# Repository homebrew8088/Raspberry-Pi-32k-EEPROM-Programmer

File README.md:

# Raspberry-Pi-32k-EEPROM-Programmer

\
\
This is a repository for my Rapberry Pi 32k EEPROM Programmer.

The [code](https://github.com/homebrew8088/Raspberry-Pi-32k-EEPROM-Programmer/tree/main/py) is written in python. To run it from the command line type "python3 32k.py"

I have included my [Kicad Files](https://github.com/homebrew8088/Raspberry-Pi-32k-EEPROM-Programmer/tree/main/Kicad) where you can find the schematics and PCB layout.

https://www.homebrew8088.com/home/28c256-eeprom-writer

This was developed to be a cheap alternative for writing 32k EEPROMs for my 8088 projects. You can compile and upload code in the application or just upload a precompiled file.  When using the application to compile the JMP code for an 8088 is automatically inserted at address 0x7FF0.  

The project uses\
1 - Raspberry PI\
2 - MCP23S17 SPI I/O’s\
1 - 28 pin ZIF\
1 - PCB\
3 - 10k resistors 

Trouble shoot \
-make sure SPI is enabled on the raspberry pi \
-install nasm on the raspberry pi

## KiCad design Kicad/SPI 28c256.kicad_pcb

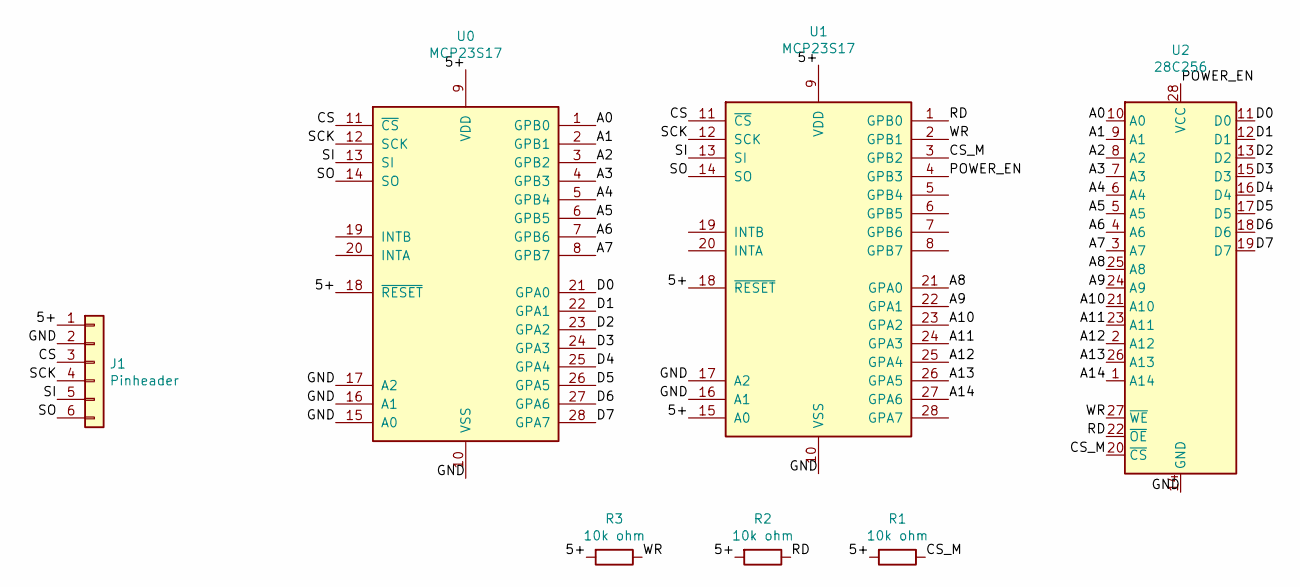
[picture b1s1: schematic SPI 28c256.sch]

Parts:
J1: Pinheader; PinHeader_1x06_P2.54mm_Vertical
R1, R2, R3: 10k ohm; R_Axial_DIN0207_L6.3mm_D2.5mm_P10.16mm_Horizontal
U0, U1: MCP23S17; DIP-28_W7.62mm
U2: 28C256; DIP_Socket-28_W11.9_W12.7_W15.24_W17.78_W18.5_3M_228-1277-0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

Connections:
/5+: J1.1, R1.2, R2.2, R3.2, U0.9 (VDD), U0.18 (~RESET~), U1.9 (VDD), U1.15 (A0), U1.18 (~RESET~)
/A0: U0.1 (GPB0), U2.10 (A0)
/A1: U0.2 (GPB1), U2.9 (A1)
/A2: U0.3 (GPB2), U2.8 (A2)
/A3: U0.4 (GPB3), U2.7 (A3)
/A4: U0.5 (GPB4), U2.6 (A4)
/A5: U0.6 (GPB5), U2.5 (A5)
/A6: U0.7 (GPB6), U2.4 (A6)
/A7: U0.8 (GPB7), U2.3 (A7)
/A8: U1.21 (GPA0), U2.25 (A8)
/A9: U1.22 (GPA1), U2.24 (A9)
/A10: U1.23 (GPA2), U2.21 (A10)
/A11: U1.24 (GPA3), U2.23 (A11)
/A12: U1.25 (GPA4), U2.2 (A12)
/A13: U1.26 (GPA5), U2.26 (A13)
/A14: U1.27 (GPA6), U2.1 (A14)
/CS: J1.3, U0.11 (~CS~), U1.11 (~CS~)
/CS_M: R1.1, U1.3 (GPB2), U2.20 (~CS)
/D0: U0.21 (GPA0), U2.11 (D0)
/D1: U0.22 (GPA1), U2.12 (D1)
/D2: U0.23 (GPA2), U2.13 (D2)
/D3: U0.24 (GPA3), U2.15 (D3)
/D4: U0.25 (GPA4), U2.16 (D4)
/D5: U0.26 (GPA5), U2.17 (D5)
/D6: U0.27 (GPA6), U2.18 (D6)
/D7: U0.28 (GPA7), U2.19 (D7)
/GND: J1.2, U0.10 (VSS), U0.15 (A0), U0.16 (A1), U0.17 (A2), U1.10 (VSS), U1.16 (A1), U1.17 (A2), U2.14 (GND)
/POWER_EN: U1.4 (GPB3), U2.28 (VCC)
/RD: R2.1, U1.1 (GPB0), U2.22 (~OE)
/SCK: J1.4, U0.12 (SCK), U1.12 (SCK)
/SI: J1.5, U0.13 (SI), U1.13 (SI)
/SO: J1.6, U0.14 (SO), U1.14 (SO)
/WR: R3.1, U1.2 (GPB1), U2.27 (~WE)

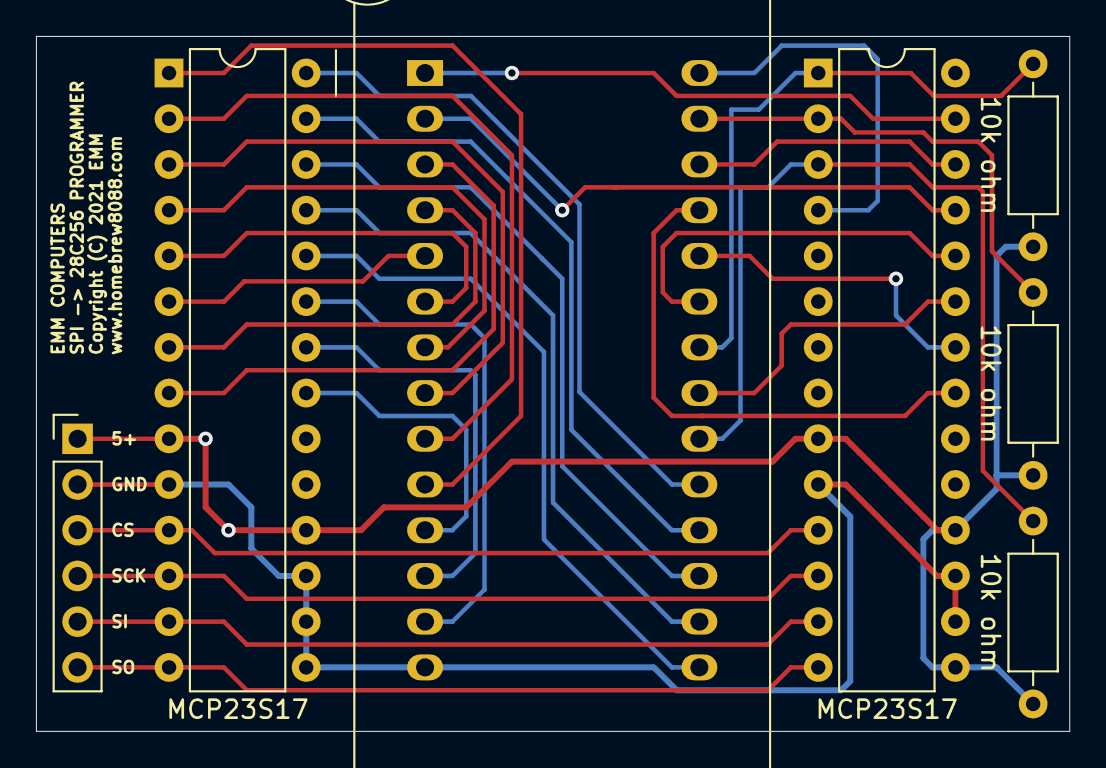
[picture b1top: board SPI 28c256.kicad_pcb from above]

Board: 2 copper layers, 57.4 x 38.6 mm, 7 parts (0 on the bottom side), 33 nets.

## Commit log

2021-11-08 initial upload
2021-11-09 Added Kicad Files
2021-11-09 Fixed Label
2021-11-10 Added .bin and .rom by default in upload file dialog
2021-11-11 Added image to README.md

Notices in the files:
Kicad/SPI 28c256.kicad_pcb:
Copyright (C) 2021 EMM
